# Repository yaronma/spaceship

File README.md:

# NOTICE -- This is work in progress -- Do not (!!) use this code or fragments of it!!!

# Spaceship
The root of the Spaceship Project.

This project is composed of the following sub-projects:
# spaceship-rpi
The Python-based spaceship logic and remote web-control implementation running on the Raspberry-Pi (any model)
# spaceship-arduino
The Arduino-based hardware control module
# spaceship-hardware
The proprietary hardware modules: 
#### The actuator control (Based on ULN2003A)
#### The fuel and oxygen levels bar-graph display (Based on MAX7219)

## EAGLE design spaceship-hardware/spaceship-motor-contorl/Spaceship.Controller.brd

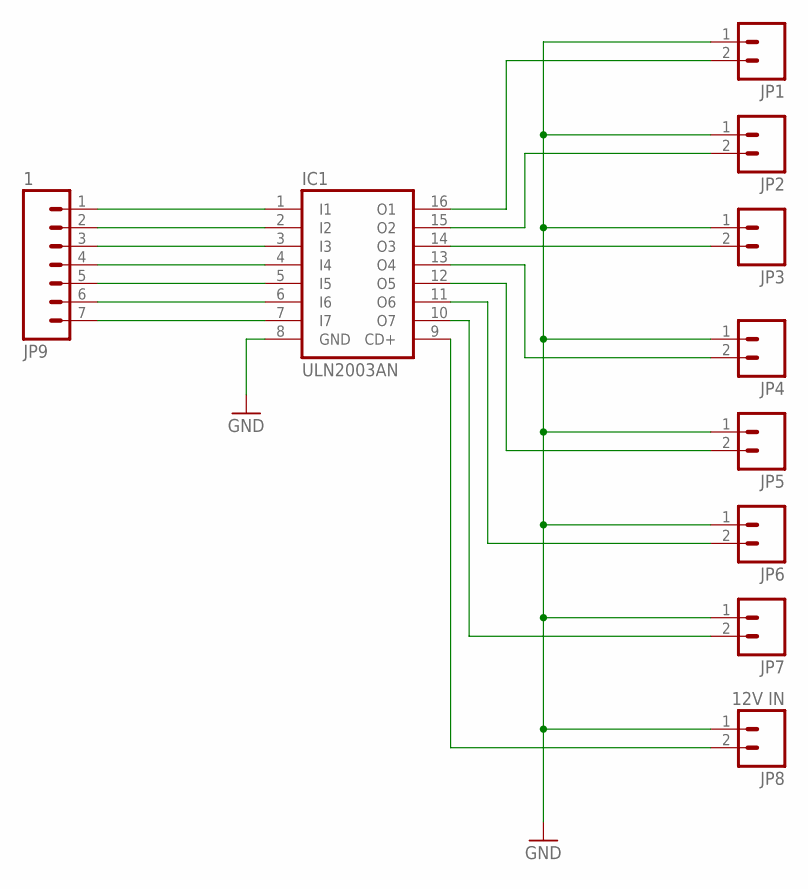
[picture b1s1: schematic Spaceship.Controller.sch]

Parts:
IC1: ULN2003AN; DIL16
JP1, JP2, JP3, JP4, JP5, JP6, JP7: M023.5MM_LOCK; SCREWTERMINAL-3.5MM-2_LOCK
JP8: 12V IN; SCREWTERMINAL-3.5MM-2_LOCK
JP9: 1; 1X07_LONGPADS

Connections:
GND: IC1.8 (GND), JP1.1, JP2.1, JP3.1, JP4.1, JP5.1, JP6.1, JP7.1, JP8.1
unnamed: IC1.13 (O4), JP4.2
unnamed: IC1.9 (CD+), JP8.2
unnamed: IC1.1 (I1), JP9.1
unnamed: IC1.2 (I2), JP9.2
unnamed: IC1.12 (O5), JP5.2
unnamed: IC1.3 (I3), JP9.3
unnamed: IC1.4 (I4), JP9.4
unnamed: IC1.5 (I5), JP9.5
unnamed: IC1.11 (O6), JP6.2
unnamed: IC1.10 (O7), JP7.2
unnamed: IC1.6 (I6), JP9.6
unnamed: IC1.14 (O3), JP3.2
unnamed: IC1.15 (O2), JP2.2
unnamed: IC1.16 (O1), JP1.2
unnamed: IC1.7 (I7), JP9.7

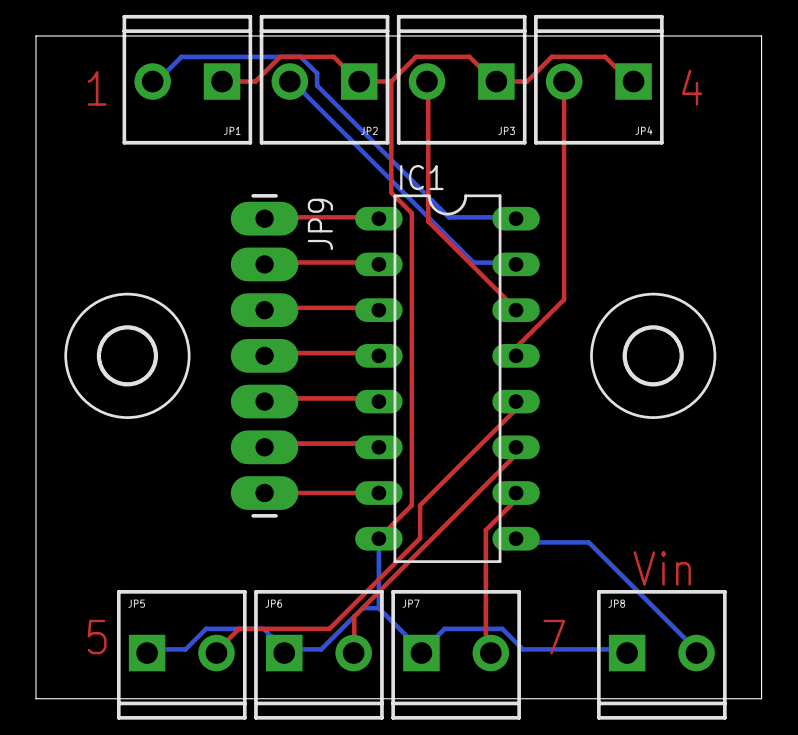
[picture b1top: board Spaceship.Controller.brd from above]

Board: 2 copper layers, 40.3 x 36.8 mm, 12 parts (0 on the bottom side), 16 nets.

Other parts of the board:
H3, H4: 3,0

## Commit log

2015-06-15 :neckbeard: Added .gitattributes & .gitignore files
2015-06-15 Baseline
2015-06-15 Baseline
    The Spaceship actuator (motor) control based on the good old ULN2003A
2015-06-15 Added ignored files
2015-06-22 Bug Fixes
2015-06-22 Fixed all LEDs Pins
2015-06-27 Fixed Motor Control
2015-06-27 Added RPi On Indication
2015-07-02 Fixed oxygen led control
2015-07-02 New Sound Usage
2015-07-02 Add Dummy RPi GPIO support
2015-07-05 Refactoring
2015-07-06 New Sounds
2015-07-06 New sound files
2015-07-06 Sound system fixes
2016-01-13 Cleanup
2016-02-28 Added control-panel image

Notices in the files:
parts and their libraries:
SparkFun-Connectors: Licensing: Creative Commons ShareAlike 4.0 International - https://creativecommons.org/licenses/by-sa/4.0
